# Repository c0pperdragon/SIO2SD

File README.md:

# SIO2SD
An Arduino-based floppy drive emulator for the Atari 8 bit computers.

This small Arduino build emulates an Atari 1050 floppy drive to connect
to an original Atari 8-bit computer. The program is compatible with
most Arduino boards. And for boards based on the Atmega32u4 it also provides
various log messages on the serial monitor to help debugging (mainly for my own use).

For a breadboard setup like my development device, you will need two push buttons,
two 7-digit LEDs and one SDCard socket (with built-in or separate level shifters) and
some wires and resistors. The connectivity is pretty standard and you will find
the details as comments in the source code.

For a more polished product, I have designed a PCB that can fit into a 3D-printed
case that resembles a tiny floppy drive with the SD card acting as a tiny floppy disk.

## Emulated floppies on SDcard
The floppy drive emulator needs an SDcard containing .ats files for each individual floppy disk.
Because there is no elaborated user-interface on the device, the naming and location of the files
need to follow a fixed system: The files are searched for in a directory ATARI/
on the root of the SDcard. Every disk file must be named nn_Anything.ats with two leading digits that correspond to the
numeric display on the device and the mandatory '_' character. Alternatively you can also
have a folder named nn_Anything with individual files inside. Such a folder will be emulated
as an read-only enhanced density floppy containing these files.

Currently only a very basic support for single density (720 sectors)
and enhanced density (1040 sectors) floppies is provided without special functions for any third-party devices.

## User interface
You can switch though the numbered disks 00 to 99 with the two buttons. This is the maximum number of disks 
supported on a single SDcard. When you switch beyond 99, you will see -- on the display, which means the device
now emulates a switched off floppy drive. Selecting a number for which no diskfile exists will simulate 
a device with no floppy inserted (in this case you can create a diskfile with the DOS format functions).

You can also emulate a second floppy drive, which is very usable for example for holding the save disks
for games that support this. To do so, you need to press both buttons to make the small indicator dot appear
on the left LCD block. This means that the number you see in the display is the floppy that is inserted
in drive 2. This floppy can now also be changed with the two buttons. It is even possible to select the same 
floppy in both drives at once (but this is probably of no great use).

## Latest hardware

## 3D-printed case

My brother went to greate lengths, designing a proper case for the floppy emulator. 
In my oppinion, this now looks absolutely phantastic.

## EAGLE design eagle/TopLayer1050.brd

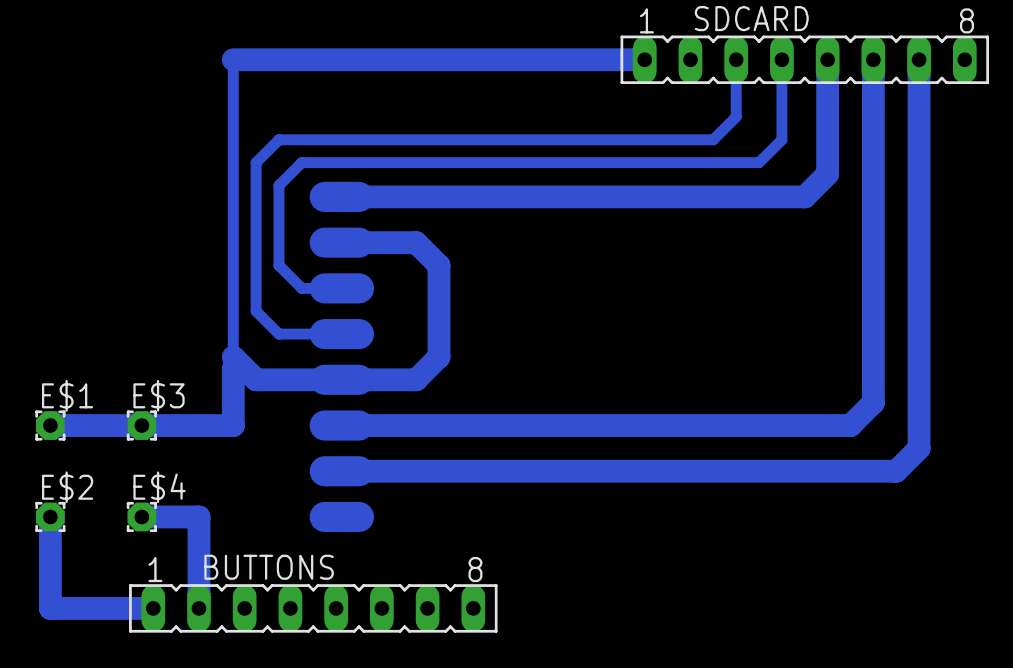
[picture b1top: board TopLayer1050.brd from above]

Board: 2 copper layers, 6 parts (0 on the bottom side), 3 nets.

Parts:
BUTTONS: FE08
E$1, E$2, E$3, E$4: 1,6/0,8
SDCARD: FE08

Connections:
S$3: BUTTONS.2, E$4.1
S$4: BUTTONS.1, E$2.1
S$15: E$1.1, E$3.1, SDCARD.1

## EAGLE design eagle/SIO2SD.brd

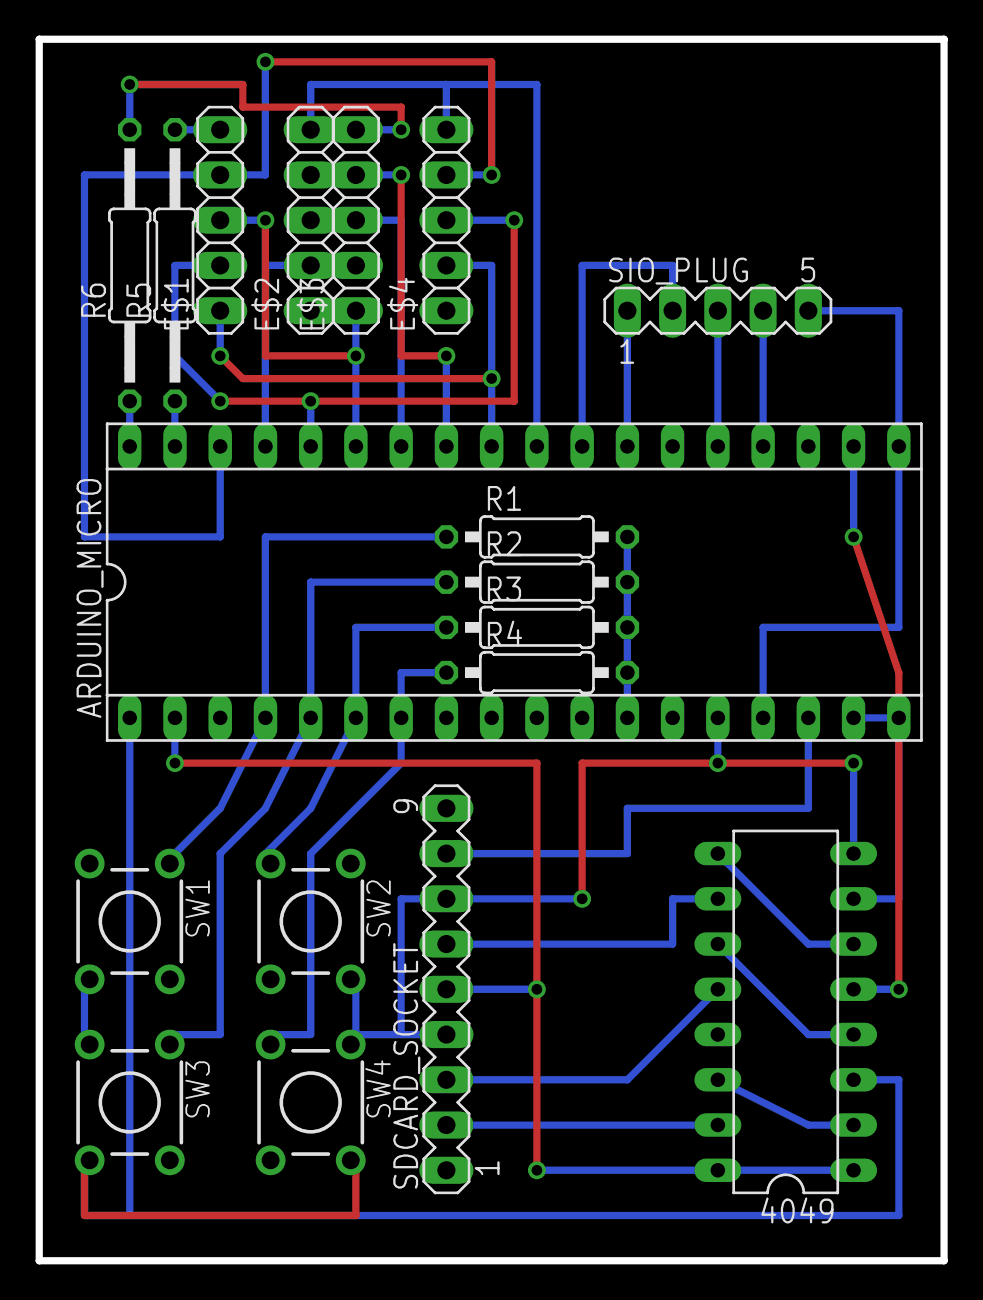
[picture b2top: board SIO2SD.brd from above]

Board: 2 copper layers, 50.8 x 68.6 mm, 18 parts (0 on the bottom side), 34 nets.

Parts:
4049: DIL16
ARDUINO_MICRO: SOCKET-36
E$1, E$2, E$3, E$4: 1X05
R1, R2, R3, R4: 10K; 0207/10
R5, R6: 150; 0207/15
SDCARD_SOCKET: MA09-1
SIO_PLUG: MA05-1
SW1, SW2, SW3, SW4: TL1105

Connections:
3V: 4049.1, 4049.16, ARDUINO_MICRO.2, SDCARD_SOCKET.5
5V: ARDUINO_MICRO.12, R1.2, R2.2, R3.2, R4.2
CLK: 4049.10, SDCARD_SOCKET.6
CMD: 4049.12, SDCARD_SOCKET.3
DAT3: 4049.15, SDCARD_SOCKET.2
DATA_IN: ARDUINO_MICRO.22, SIO_PLUG.4
DATA_OUT: ARDUINO_MICRO.23, SIO_PLUG.3
GND: 4049.8, ARDUINO_MICRO.14, SDCARD_SOCKET.4, SDCARD_SOCKET.7
MISO: ARDUINO_MICRO.16, SDCARD_SOCKET.8
MOSI: 4049.5, ARDUINO_MICRO.20
S$1: ARDUINO_MICRO.5, R2.1
S$3: 4049.6, 4049.9
S$4: 4049.4, 4049.11
S$5: 4049.2, 4049.14
S$6: ARDUINO_MICRO.26, SIO_PLUG.2
S$7: ARDUINO_MICRO.25, SIO_PLUG.1
S$10: ARDUINO_MICRO.34, E$1.4, E$4.4
S$11: ARDUINO_MICRO.29, E$2.4, E$3.4
S$13: ARDUINO_MICRO.4, R1.1
S$15: ARDUINO_MICRO.31, E$1.3, E$3.1
S$16: ARDUINO_MICRO.7, R4.1
S$17: ARDUINO_MICRO.33, E$2.2, E$3.2
S$18: ARDUINO_MICRO.36, R6.1
S$19: ARDUINO_MICRO.27, E$2.5, E$4.5
S$20: ARDUINO_MICRO.28, E$1.1, E$4.2
S$21: ARDUINO_MICRO.30, E$2.3, E$3.3
S$22: ARDUINO_MICRO.35, R5.1
S$23: E$1.5, R5.2
S$24: E$3.5, R6.2
S$25: ARDUINO_MICRO.32, E$1.2, E$4.3
S$28: ARDUINO_MICRO.6, R3.1
SCK: 4049.7, ARDUINO_MICRO.17
SS: 4049.3, ARDUINO_MICRO.1
VIN: ARDUINO_MICRO.15, SIO_PLUG.5

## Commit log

2015-08-21 Initial check-in
2015-08-21 extended readme and fixed board layout
2015-08-21 moved code, fixed bugs
2015-09-02 Picture gallery
2016-07-05 archive some rom files
2016-08-21 Prepare more disk files
2016-08-21 Support emulation for multiple floppy drives (D1- D8).
2016-09-06 Mini floppy device
    Board design and adapted arduino sketch (supports large and mini boards)
2016-09-09 changed button assignment for mini1080
2016-09-10 Key repeat for disk change buttons.
2017-03-15 Breadboard version
    Cleaned up the code a bit, removed support for first board design.
2018-03-17 Disk folder reorganization
    To prepare for future changes in the button interface, I have flattened
    and restructured the floppy directory and renamed it to ATARI to match
    the folder name on the SDCARD
2018-03-17 Changed user interface
2018-03-18 Emulate formatting of single and medium density floppies
2018-04-02 Support using directories as disks
2018-04-06 Error state if SDcard not present at startup
2018-04-07 Tweak program to start up fast again
    Instead of initializing SDcard before everything else, defer this until
    actual disk access is done. This is necessary to make the SIO2SD device
    respond immediately to the booting atari.
2018-04-08 Start designing PCB for small SIO2SD variant
2018-04-14 Single board device design
2018-04-15 Change reset circuit, layout fixes
2018-04-15 Small layout fixes, Gerber files
2018-04-16 Docu
2018-04-22 Allow multi-slave configuration
    By inserting a diode into TX -> Data In, the device can emulate an open
    collector to not interfer with other devices on the same bus.
2018-05-05 Remove dependency on external library
2020-08-01 Bring design files to new KiCAD version. Create gerber files.
2020-08-27 3D-printed case, more images.
2020-08-28 formatting
2020-09-02 Small 256 color demo program
2023-06-27 Add the FujuBoink! demo
2023-09-28 Add program: "Atari Control Picture"
